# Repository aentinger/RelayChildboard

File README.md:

💾 Relay Childboard
===================

# 📸 Image

# 📂 Description

The LXRobotics Relay Childboard allows to turn on/off a load via a relay. The switching status of the relay is visualized by a red status LED. High quality screw terminals ensure stable and durable connection. For a quick and easy start, an open source Arduino library with sample programs is available.

**Features**

* Control a single load via a relay
* Max current. 10 A
* Max. DC voltage: 24 V DC
* Max. AC voltage: 250 V AC
* Relay-Type: SPDT (Single Pole commutator)
* Red signal LED shows relay status (ON/OFF)
* Optocouplers insulate Arduino from Relay circuit
* High quality screw terminals
* Can be used with the Radioshield the Childboard Adaptershield
* Arduino Library with example programs is available on GitHub

# 🎥 [Video](images/childboard_relay_demo.mp4)

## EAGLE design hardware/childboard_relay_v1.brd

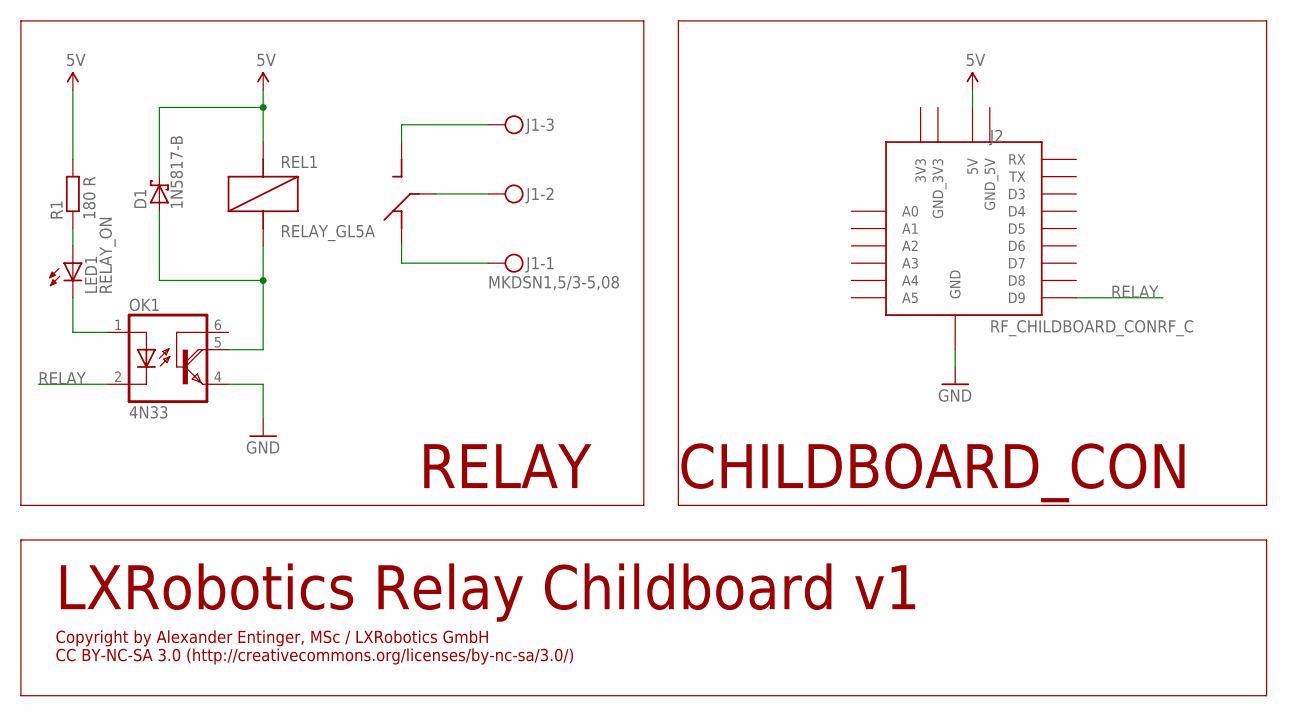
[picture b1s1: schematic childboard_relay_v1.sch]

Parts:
D1: 1N5817-B; DO41-7.6
J1: MKDSN1,5/3-5,08
J2: RF_CHILDBOARD_CONRF_C; RF_CHILDBOARD_CON
LED1: RELAY_ON; LED5MM
OK1: 4N33; DIL06
R1: 180 R; 0204/7
REL1: RELAY_GL5A

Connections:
5V: D1.C, J2.5V, R1.2, REL1.R2 (R2_COIL1)
GND: J2.GND_ (GND), OK1.4 (E)
unnamed: J1.2, REL1.R1 (R1_COMMON)
unnamed: J1.3, REL1.R3 (R3_SW)
unnamed: J1.1, REL1.R4 (R4_SW)
unnamed: LED1.K (C), OK1.1 (A)
unnamed: D1.A, OK1.5 (COL), REL1.R5 (R5_COIL2)
unnamed: LED1.A, R1.1
RELAY: J2.D9, OK1.2 (C)

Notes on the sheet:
RELAY
CHILDBOARD_CON
LXRobotics Relay Childboard v1
Copyright by Alexander Entinger, MSc / LXRobotics GmbH CC BY-NC-SA 3.0 (http://creativecommons.org/licenses/by-nc-sa/3.0/)

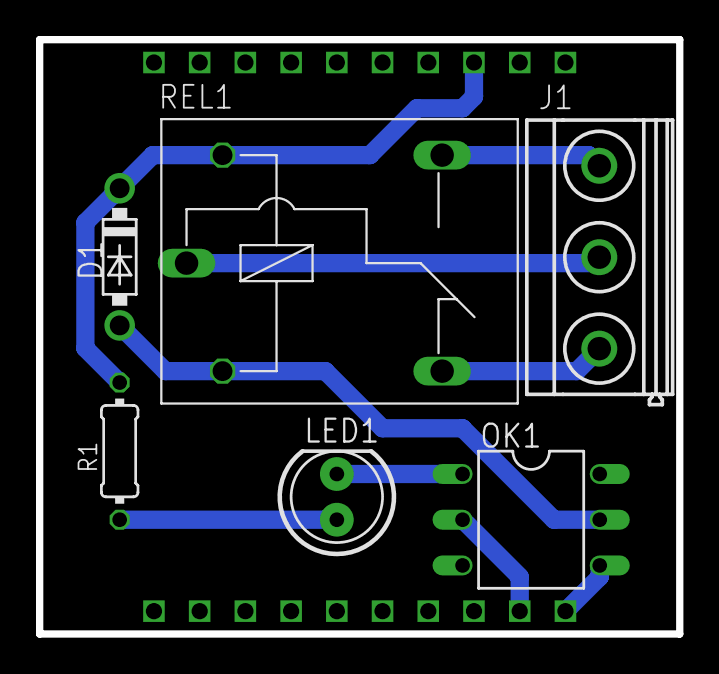
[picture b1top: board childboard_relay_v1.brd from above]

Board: 2 copper layers, 35.6 x 33.0 mm, 7 parts (0 on the bottom side), 9 nets.

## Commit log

2014-06-04 initial checkin of lxr chilboard relay repo data
2014-06-04 adding serial relay control example
2017-06-27 Adding hardware + images
2025-03-26 Upload BOM.
2025-03-26 Add demo video.
2025-03-26 Pretty up README.

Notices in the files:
README.md:
License: CC BY-NC-SA 4.0
parts and their libraries:
SparkFun-LED: Licensing: CC v3.0 Share-Alike You are welcome to use this library for commercial purposes.
